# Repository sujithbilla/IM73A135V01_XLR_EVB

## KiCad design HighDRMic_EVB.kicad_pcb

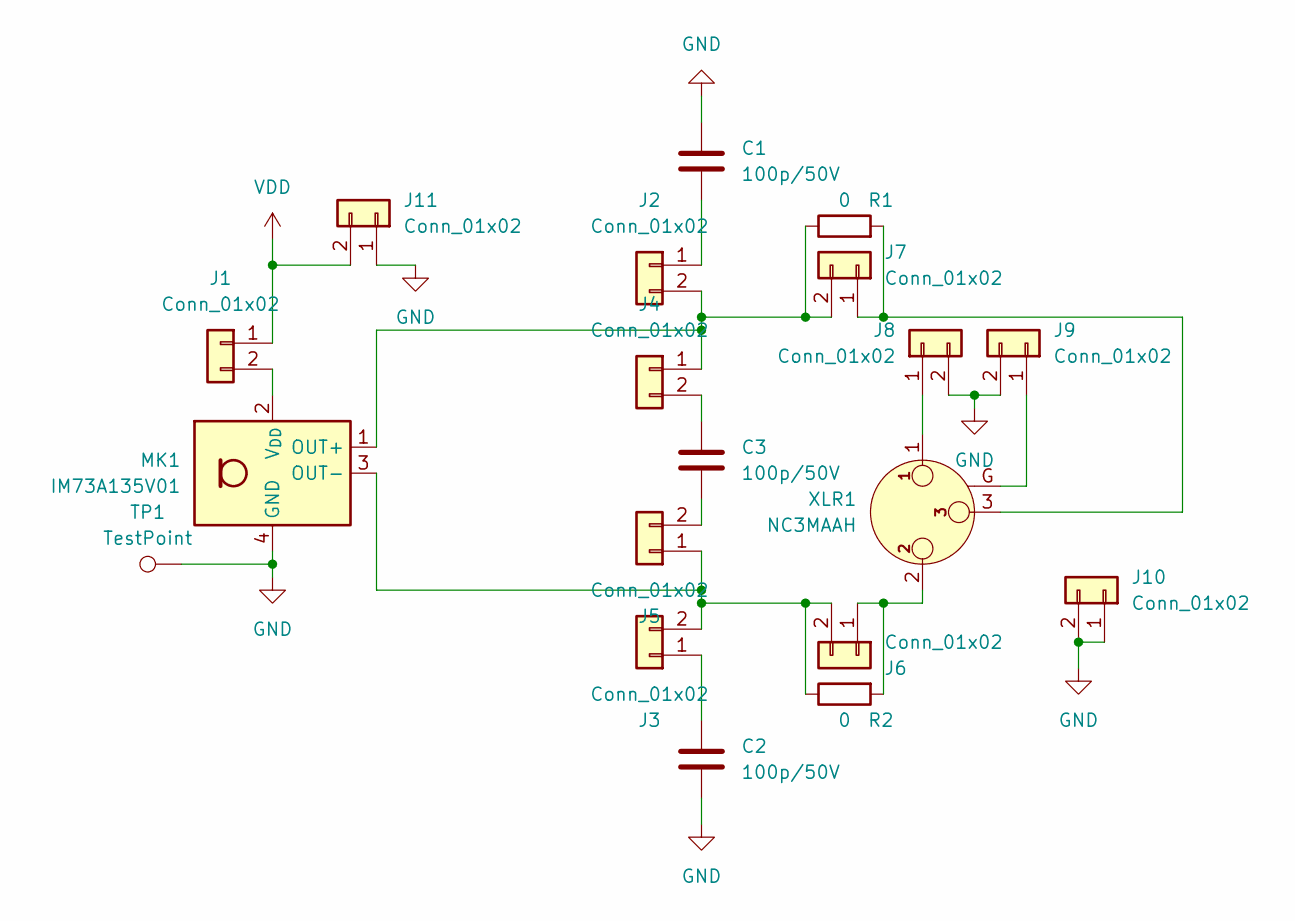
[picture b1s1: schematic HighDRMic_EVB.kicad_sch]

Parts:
C1, C2, C3: 100p/50V; C_0201_0603Metric_Pad0.64x0.40mm_HandSolder
J1, J2, J3, J4, J5, J6, J7, J8, J9, J10, J11: Conn_01x02; PinHeader_1x02_P2.54mm_Vertical
MK1: IM73A135V01; Infineon_PG-LLGA-5-2
R1, R2: 0; R_0201_0603Metric_Pad0.64x0.40mm_HandSolder
TP1: TestPoint; TestPoint_THTPad_D1.5mm_Drill0.7mm
XLR1: NC3MAAH; Jack_XLR_Neutrik_NC3MAAH_Horizontal

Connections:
GND: C1.1, C2.2, J8.2, J9.2, J10.1, J10.2, J11.1, MK1.4 (GND), MK1.5 (GND), TP1.1
unnamed: J1.2, MK1.2 (V_{DD})
unnamed: C1.2, J2.1
unnamed: J2.2, J4.1, J7.2, MK1.1 (OUT+), R1.1
unnamed: C2.1, J3.1
unnamed: J3.2, J5.1, J6.2, MK1.3 (OUT-), R2.1
unnamed: C3.1, J4.2
unnamed: C3.2, J5.2
unnamed: J6.1, R2.2, XLR1.2
unnamed: J7.1, R1.2, XLR1.3
unnamed: J8.1, XLR1.1
unnamed: J9.1, XLR1.G
VDD: J1.1, J11.2

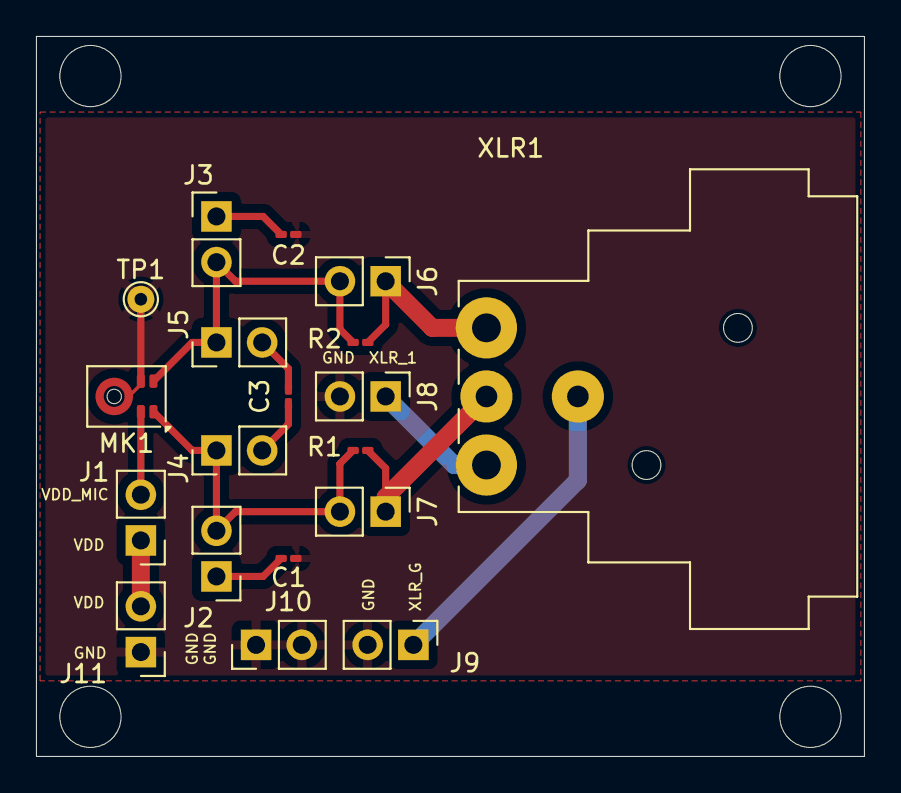
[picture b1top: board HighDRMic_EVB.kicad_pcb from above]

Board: 2 copper layers, 46.0 x 40.0 mm, 19 parts (0 on the bottom side), 13 nets.

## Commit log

2025-03-05 Adding schematic and pcb files - zeroeth version
2025-03-05 Adding gerber files
2025-03-05 Adding ODB++ and IPC-2581 files
2025-03-05 Adding gerber/drill file archive
2025-03-05 Added schematic pdf
2025-03-05 Added 3D png
